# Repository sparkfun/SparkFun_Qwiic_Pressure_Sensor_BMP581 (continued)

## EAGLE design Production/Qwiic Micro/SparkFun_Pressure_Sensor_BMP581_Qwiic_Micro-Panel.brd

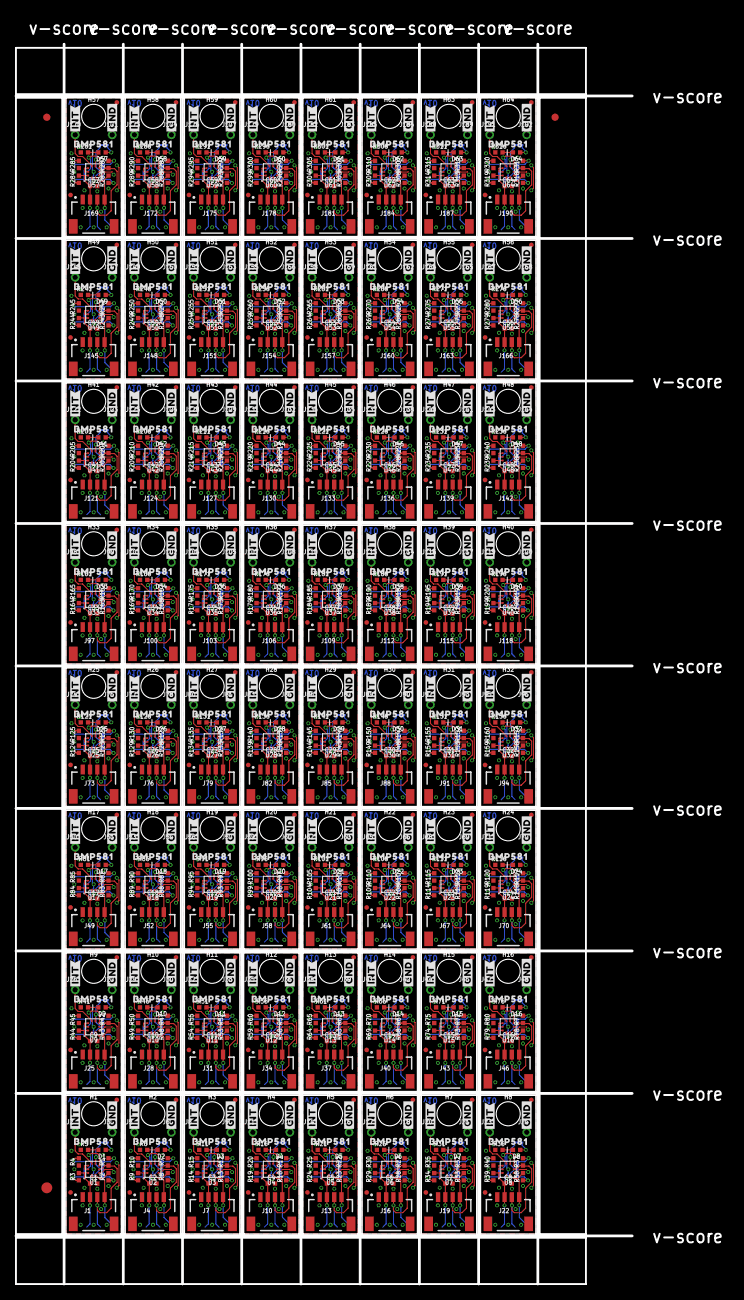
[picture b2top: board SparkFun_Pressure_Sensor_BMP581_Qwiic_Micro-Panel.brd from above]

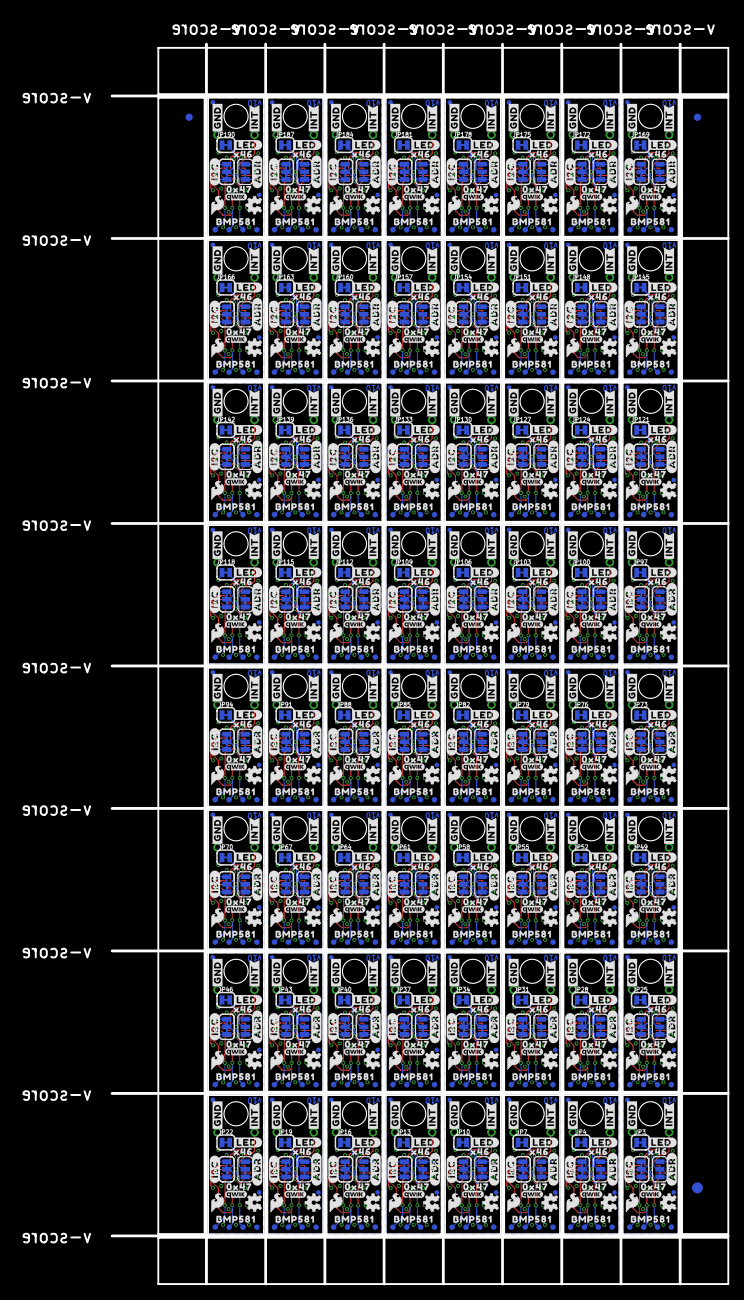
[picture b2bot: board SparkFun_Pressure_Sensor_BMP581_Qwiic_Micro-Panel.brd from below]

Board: 2 copper layers, 84.6 x 170.2 mm, 2502 parts (1283 on the bottom side), 768 nets.

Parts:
C1, C2, C3, C4, C5, C6, C7, C8, C9, C10, C11, C12, C13, C14, C15, C16, C17, C18, C19, C20, C21, C22, C23, C24, C25, C26, C27, C28, C29, C30, C31, C32, C33, C34, C35, C36, C37, C38, C39, C40, C41, C42, C43, C44, C45, C46, C47, C48, C49, C50, C51, C52, C53, C54, C55, C56, C57, C58, C59, C60, C61, C62, C63, C64: 0.1uF; 0402-TIGHT
D1, D2, D3, D4, D5, D6, D7, D8, D9, D10, D11, D12, D13, D14, D15, D16, D17, D18, D19, D20, D21, D22, D23, D24, D25, D26, D27, D28, D29, D30, D31, D32, D33, D34, D35, D36, D37, D38, D39, D40, D41, D42, D43, D44, D45, D46, D47, D48, D49, D50, D51, D52, D53, D54, D55, D56, D57, D58, D59, D60, D61, D62, D63, D64: RED; LED-0402
E$1, E$2, E$3, E$4: FIDUCIAL-1X2
E$5, E$6: FIDUCIAL-1.5X3
FD1, FD2, FD3, FD4, FD5, FD6, FD7, FD8, FD9, FD10, FD11, FD12, FD13, FD14, FD15, FD16, FD17, FD18, FD19, FD20, FD21, FD22, FD23, FD24, FD25, FD26, FD27, FD28, FD29, FD30, FD31, FD32, FD33, FD34, FD35, FD36, FD37, FD38, FD39, FD40, FD41, FD42, FD43, FD44, FD45, FD46, FD47, FD48, FD49, FD50, FD51, FD52, FD53, FD54, FD55, FD56, FD57, FD58, FD59, FD60, FD61, FD62, FD63, FD64, FD65, FD66, FD67, FD68, FD69, FD70, FD71, FD72, FD73, FD74, FD75, FD76, FD77, FD78, FD79, FD80, FD81, FD82, FD83, FD84, FD85, FD86, FD87, FD88, FD89, FD90, FD91, FD92, FD93, FD94, FD95, FD96, FD97, FD98, FD99, FD100, FD101, FD102, FD103, FD104, FD105, FD106, FD107, FD108, FD109, FD110, FD111, FD112, FD113, FD114, FD115, FD116, FD117, FD118, FD119, FD120, FD121, FD122, FD123, FD124, FD125, FD126, FD127, FD128, FD129, FD130, FD131, FD132, FD133, FD134, FD135, FD136, FD137, FD138, FD139, FD140, FD141, FD142, FD143, FD144, FD145, FD146, FD147, FD148, FD149, FD150, FD151, FD152, FD153, FD154, FD155, FD156, FD157, FD158, FD159, FD160, FD161, FD162, FD163, FD164, FD165, FD166, FD167, FD168, FD169, FD170, FD171, FD172, FD173, FD174, FD175, FD176, FD177, FD178, FD179, FD180, FD181, FD182, FD183, FD184, FD185, FD186, FD187, FD188, FD189, FD190, FD191, FD192, FD193, FD194, FD195, FD196, FD197, FD198, FD199, FD200, FD201, FD202, FD203, FD204, FD205, FD206, FD207, FD208, FD209, FD210, FD211, FD212, FD213, FD214, FD215, FD216, FD217, FD218, FD219, FD220, FD221, FD222, FD223, FD224, FD225, FD226, FD227, FD228, FD229, FD230, FD231, FD232, FD233, FD234, FD235, FD236, FD237, FD238, FD239, FD240, FD241, FD242, FD243, FD244, FD245, FD246, FD247, FD248, FD249, FD250, FD251, FD252, FD253, FD254, FD255, FD256: FIDUCIALUFIDUCIAL; FIDUCIAL-MICRO
FRAME1, FRAME2, FRAME3, FRAME4, FRAME5, FRAME6, FRAME7, FRAME8, FRAME9, FRAME10, FRAME11, FRAME12, FRAME13, FRAME14, FRAME15, FRAME16, FRAME17, FRAME18, FRAME19, FRAME20, FRAME21, FRAME22, FRAME23, FRAME24, FRAME25, FRAME26, FRAME27, FRAME28, FRAME29, FRAME30, FRAME31, FRAME32, FRAME33, FRAME34, FRAME35, FRAME36, FRAME37, FRAME38, FRAME39, FRAME40, FRAME41, FRAME42, FRAME43, FRAME44, FRAME45, FRAME46, FRAME47, FRAME48, FRAME49, FRAME50, FRAME51, FRAME52, FRAME53, FRAME54, FRAME55, FRAME56, FRAME57, FRAME58, FRAME59, FRAME60, FRAME61, FRAME62, FRAME63, FRAME64: FRAME-LETTER; CREATIVE_COMMONS
H1, H2, H3, H4, H5, H6, H7, H8, H9, H10, H11, H12, H13, H14, H15, H16, H17, H18, H19, H20, H21, H22, H23, H24, H25, H26, H27, H28, H29, H30, H31, H32, H33, H34, H35, H36, H37, H38, H39, H40, H41, H42, H43, H44, H45, H46, H47, H48, H49, H50, H51, H52, H53, H54, H55, H56, H57, H58, H59, H60, H61, H62, H63, H64: STAND-OFF
J1, J4, J7, J10, J13, J16, J19, J22, J25, J28, J31, J34, J37, J40, J43, J46, J49, J52, J55, J58, J61, J64, J67, J70, J73, J76, J79, J82, J85, J88, J91, J94, J97, J100, J103, J106, J109, J112, J115, J118, J121, J124, J127, J130, J133, J136, J139, J142, J145, J148, J151, J154, J157, J160, J163, J166, J169, J172, J175, J178, J181, J184, J187, J190: QWIIC_RIGHT_ANGLE; JST04_1MM_RA
J2, J3, J5, J6, J8, J9, J11, J12, J14, J15, J17, J18, J20, J21, J23, J24, J26, J27, J29, J30, J32, J33, J35, J36, J38, J39, J41, J42, J44, J45, J47, J48, J50, J51, J53, J54, J56, J57, J59, J60, J62, J63, J65, J66, J68, J69, J71, J72, J74, J75, J77, J78, J80, J81, J83, J84, J86, J87, J89, J90, J92, J93, J95, J96, J98, J99, J101, J102, J104, J105, J107, J108, J110, J111, J113, J114, J116, J117, J119, J120, J122, J123, J125, J126, J128, J129, J131, J132, J134, J135, J137, J138, J140, J141, J143, J144, J146, J147, J149, J150, J152, J153, J155, J156, J158, J159, J161, J162, J164, J165, J167, J168, J170, J171, J173, J174, J176, J177, J179, J180, J182, J183, J185, J186, J188, J189, J191, J192: 1X01_1MM_NO_SILK
JP1, JP6, JP9, JP12, JP15, JP18, JP21, JP24, JP27, JP30, JP33, JP36, JP39, JP42, JP45, JP48, JP51, JP54, JP57, JP60, JP63, JP66, JP69, JP72, JP75, JP78, JP81, JP84, JP87, JP90, JP93, JP96, JP99, JP102, JP105, JP108, JP111, JP114, JP117, JP120, JP123, JP126, JP129, JP132, JP135, JP138, JP141, JP144, JP147, JP150, JP153, JP156, JP159, JP162, JP165, JP168, JP171, JP174, JP177, JP180, JP183, JP186, JP189, JP192: ADR; SMT-JUMPER_3_1-NC_TRACE_SILK
JP2, JP5, JP8, JP11, JP14, JP17, JP20, JP23, JP26, JP29, JP32, JP35, JP38, JP41, JP44, JP47, JP50, JP53, JP56, JP59, JP62, JP65, JP68, JP71, JP74, JP77, JP80, JP83, JP86, JP89, JP92, JP95, JP98, JP101, JP104, JP107, JP110, JP113, JP116, JP119, JP122, JP125, JP128, JP131, JP134, JP137, JP140, JP143, JP146, JP149, JP152, JP155, JP158, JP161, JP164, JP167, JP170, JP173, JP176, JP179, JP182, JP185, JP188, JP191: I2C; SMT-JUMPER_3_2-NC_TRACE_SILK
JP3, JP4, JP7, JP10, JP13, JP16, JP19, JP22, JP25, JP28, JP31, JP34, JP37, JP40, JP43, JP46, JP49, JP52, JP55, JP58, JP61, JP64, JP67, JP70, JP73, JP76, JP79, JP82, JP85, JP88, JP91, JP94, JP97, JP100, JP103, JP106, JP109, JP112, JP115, JP118, JP121, JP124, JP127, JP130, JP133, JP136, JP139, JP142, JP145, JP148, JP151, JP154, JP157, JP160, JP163, JP166, JP169, JP172, JP175, JP178, JP181, JP184, JP187, JP190: LED; SMT-JUMPER_2_NC_TRACE_SILK
LOGO1, LOGO5, LOGO9, LOGO13, LOGO17, LOGO21, LOGO25, LOGO29, LOGO33, LOGO37, LOGO41, LOGO45, LOGO49, LOGO53, LOGO57, LOGO61, LOGO65, LOGO69, LOGO73, LOGO77, LOGO81, LOGO85, LOGO89, LOGO93, LOGO97, LOGO101, LOGO105, LOGO109, LOGO113, LOGO117, LOGO121, LOGO125, LOGO129, LOGO133, LOGO137, LOGO141, LOGO145, LOGO149, LOGO153, LOGO157, LOGO161, LOGO165, LOGO169, LOGO173, LOGO177, LOGO181, LOGO185, LOGO189, LOGO193, LOGO197, LOGO201, LOGO205, LOGO209, LOGO213, LOGO217, LOGO221, LOGO225, LOGO229, LOGO233, LOGO237, LOGO241, LOGO245, LOGO249, LOGO253: OSHW-LOGOMINI; OSHW-LOGO-MINI
LOGO2, LOGO6, LOGO10, LOGO14, LOGO18, LOGO22, LOGO26, LOGO30, LOGO34, LOGO38, LOGO42, LOGO46, LOGO50, LOGO54, LOGO58, LOGO62, LOGO66, LOGO70, LOGO74, LOGO78, LOGO82, LOGO86, LOGO90, LOGO94, LOGO98, LOGO102, LOGO106, LOGO110, LOGO114, LOGO118, LOGO122, LOGO126, LOGO130, LOGO134, LOGO138, LOGO142, LOGO146, LOGO150, LOGO154, LOGO158, LOGO162, LOGO166, LOGO170, LOGO174, LOGO178, LOGO182, LOGO186, LOGO190, LOGO194, LOGO198, LOGO202, LOGO206, LOGO210, LOGO214, LOGO218, LOGO222, LOGO226, LOGO230, LOGO234, LOGO238, LOGO242, LOGO246, LOGO250, LOGO254: SFE_LOGO_FLAME.1_INCH; SFE_LOGO_FLAME_.1
LOGO3, LOGO7, LOGO11, LOGO15, LOGO19, LOGO23, LOGO27, LOGO31, LOGO35, LOGO39, LOGO43, LOGO47, LOGO51, LOGO55, LOGO59, LOGO63, LOGO67, LOGO71, LOGO75, LOGO79, LOGO83, LOGO87, LOGO91, LOGO95, LOGO99, LOGO103, LOGO107, LOGO111, LOGO115, LOGO119, LOGO123, LOGO127, LOGO131, LOGO135, LOGO139, LOGO143, LOGO147, LOGO151, LOGO155, LOGO159, LOGO163, LOGO167, LOGO171, LOGO175, LOGO179, LOGO183, LOGO187, LOGO191, LOGO195, LOGO199, LOGO203, LOGO207, LOGO211, LOGO215, LOGO219, LOGO223, LOGO227, LOGO231, LOGO235, LOGO239, LOGO243, LOGO247, LOGO251, LOGO255: QWIIC_LOGO_3MM; QWIIC_3MM
LOGO4, LOGO8, LOGO12, LOGO16, LOGO20, LOGO24, LOGO28, LOGO32, LOGO36, LOGO40, LOGO44, LOGO48, LOGO52, LOGO56, LOGO60, LOGO64, LOGO68, LOGO72, LOGO76, LOGO80, LOGO84, LOGO88, LOGO92, LOGO96, LOGO100, LOGO104, LOGO108, LOGO112, LOGO116, LOGO120, LOGO124, LOGO128, LOGO132, LOGO136, LOGO140, LOGO144, LOGO148, LOGO152, LOGO156, LOGO160, LOGO164, LOGO168, LOGO172, LOGO176, LOGO180, LOGO184, LOGO188, LOGO192, LOGO196, LOGO200, LOGO204, LOGO208, LOGO212, LOGO216, LOGO220, LOGO224, LOGO228, LOGO232, LOGO236, LOGO240, LOGO244, LOGO248, LOGO252, LOGO256: SFE_LOGO_NAMEBLANK; BLANK
R1, R2, R7, R8, R12, R13, R17, R18, R22, R23, R27, R28, R32, R33, R37, R38, R42, R43, R47, R48, R52, R53, R57, R58, R62, R63, R67, R68, R72, R73, R77, R78, R82, R83, R87, R88, R92, R93, R97, R98, R102, R103, R107, R108, R112, R113, R117, R118, R122, R123, R127, R128, R132, R133, R137, R138, R142, R143, R147, R148, R152, R153, R157, R158, R162, R163, R167, R168, R172, R173, R177, R178, R182, R183, R187, R188, R192, R193, R197, R198, R202, R203, R207, R208, R212, R213, R217, R218, R222, R223, R227, R228, R232, R233, R237, R238, R242, R243, R247, R248, R252, R253, R257, R258, R262, R263, R267, R268, R272, R273, R277, R278, R282, R283, R287, R288, R292, R293, R297, R298, R302, R303, R307, R308, R312, R313, R317, R318: 2.2k; 0402-TIGHT
R3, R4, R9, R10, R14, R15, R19, R20, R24, R25, R29, R30, R34, R35, R39, R40, R44, R45, R49, R50, R54, R55, R59, R60, R64, R65, R69, R70, R74, R75, R79, R80, R84, R85, R89, R90, R94, R95, R99, R100, R104, R105, R109, R110, R114, R115, R119, R120, R124, R125, R129, R130, R134, R135, R139, R140, R144, R145, R149, R150, R154, R155, R159, R160, R164, R165, R169, R170, R174, R175, R179, R180, R184, R185, R189, R190, R194, R195, R199, R200, R204, R205, R209, R210, R214, R215, R219, R220, R224, R225, R229, R230, R234, R235, R239, R240, R244, R245, R249, R250, R254, R255, R259, R260, R264, R265, R269, R270, R274, R275, R279, R280, R284, R285, R289, R290, R294, R295, R299, R300, R304, R305, R309, R310, R314, R315, R319, R320: 10K; 0402-TIGHT
R5, R6, R11, R16, R21, R26, R31, R36, R41, R46, R51, R56, R61, R66, R71, R76, R81, R86, R91, R96, R101, R106, R111, R116, R121, R126, R131, R136, R141, R146, R151, R156, R161, R166, R171, R176, R181, R186, R191, R196, R201, R206, R211, R216, R221, R226, R231, R236, R241, R246, R251, R256, R261, R266, R271, R276, R281, R286, R291, R296, R301, R306, R311, R316: 1k; 0402-TIGHT
TP1, TP2, TP3, TP4, TP5, TP6, TP7, TP8, TP9, TP10, TP11, TP12, TP13, TP14, TP15, TP16, TP17, TP18, TP19, TP20, TP21, TP22, TP23, TP24, TP25, TP26, TP27, TP28, TP29, TP30, TP31, TP32, TP33, TP34, TP35, TP36, TP37, TP38, TP39, TP40, TP41, TP42, TP43, TP44, TP45, TP46, TP47, TP48, TP49, TP50, TP51, TP52, TP53, TP54, TP55, TP56, TP57, TP58, TP59, TP60, TP61, TP62, TP63, TP64, TP65, TP66, TP67, TP68, TP69, TP70, TP71, TP72, TP73, TP74, TP75, TP76, TP77, TP78, TP79, TP80, TP81, TP82, TP83, TP84, TP85, TP86, TP87, TP88, TP89, TP90, TP91, TP92, TP93, TP94, TP95, TP96, TP97, TP98, TP99, TP100, TP101, TP102, TP103, TP104, TP105, TP106, TP107, TP108, TP109, TP110, TP111, TP112, TP113, TP114, TP115, TP116, TP117, TP118, TP119, TP120, TP121, TP122, TP123, TP124, TP125, TP126, TP127, TP128, TP129, TP130, TP131, TP132, TP133, TP134, TP135, TP136, TP137, TP138, TP139, TP140, TP141, TP142, TP143, TP144, TP145, TP146, TP147, TP148, TP149, TP150, TP151, TP152, TP153, TP154, TP155, TP156, TP157, TP158, TP159, TP160, TP161, TP162, TP163, TP164, TP165, TP166, TP167, TP168, TP169, TP170, TP171, TP172, TP173, TP174, TP175, TP176, TP177, TP178, TP179, TP180, TP181, TP182, TP183, TP184, TP185, TP186, TP187, TP188, TP189, TP190, TP191, TP192, TP193, TP194, TP195, TP196, TP197, TP198, TP199, TP200, TP201, TP202, TP203, TP204, TP205, TP206, TP207, TP208, TP209, TP210, TP211, TP212, TP213, TP214, TP215, TP216, TP217, TP218, TP219, TP220, TP221, TP222, TP223, TP224, TP225, TP226, TP227, TP228, TP229, TP230, TP231, TP232, TP233, TP234, TP235, TP236, TP237, TP238, TP239, TP240, TP241, TP242, TP243, TP244, TP245, TP246, TP247, TP248, TP249, TP250, TP251, TP252, TP253, TP254, TP255, TP256: TEST-POINT3; PAD.03X.03
U1, U2, U3, U4, U5, U6, U7, U8, U9, U10, U11, U12, U13, U14, U15, U16, U17, U18, U19, U20, U21, U22, U23, U24, U25, U26, U27, U28, U29, U30, U31, U32, U33, U34, U35, U36, U37, U38, U39, U40, U41, U42, U43, U44, U45, U46, U47, U48, U49, U50, U51, U52, U53, U54, U55, U56, U57, U58, U59, U60, U61, U62, U63, U64: BMP581
U$1, U$2, U$16, U$17, U$27, U$28, U$38, U$39, U$49, U$50, U$60, U$61, U$71, U$72, U$82, U$83, U$93, U$94, U$104, U$105, U$115, U$116, U$126, U$127, U$137, U$138, U$148, U$149, U$159, U$160, U$170, U$171, U$181, U$182, U$192, U$193, U$203, U$204, U$214, U$215, U$225, U$226, U$236, U$237, U$247, U$248, U$258, U$259, U$269, U$270, U$280, U$281, U$291, U$292, U$302, U$303, U$313, U$314, U$324, U$325, U$335, U$336, U$346, U$347, U$357, U$358, U$368, U$369, U$379, U$380, U$390, U$391, U$401, U$402, U$412, U$413, U$423, U$424, U$434, U$435, U$445, U$446, U$456, U$457, U$467, U$468, U$478, U$479, U$489, U$490, U$500, U$501, U$511, U$512, U$522, U$523, U$533, U$534, U$544, U$545, U$555, U$556, U$566, U$567, U$577, U$578, U$588, U$589, U$599, U$600, U$610, U$611, U$621, U$622, U$632, U$633, U$643, U$644, U$654, U$655, U$665, U$666, U$676, U$677, U$687, U$688, U$698, U$699: BMP5810
U$3, U$18, U$29, U$40, U$51, U$62, U$73, U$84, U$95, U$106, U$117, U$128, U$139, U$150, U$161, U$172, U$183, U$194, U$205, U$216, U$227, U$238, U$249, U$260, U$271, U$282, U$293, U$304, U$315, U$326, U$337, U$348, U$359, U$370, U$381, U$392, U$403, U$414, U$425, U$436, U$447, U$458, U$469, U$480, U$491, U$502, U$513, U$524, U$535, U$546, U$557, U$568, U$579, U$590, U$601, U$612, U$623, U$634, U$645, U$656, U$667, U$678, U$689, U$700: #I2C#0
U$4, U$19, U$30, U$41, U$52, U$63, U$74, U$85, U$96, U$107, U$118, U$129, U$140, U$151, U$162, U$173, U$184, U$195, U$206, U$217, U$228, U$239, U$250, U$261, U$272, U$283, U$294, U$305, U$316, U$327, U$338, U$349, U$360, U$371, U$382, U$393, U$404, U$415, U$426, U$437, U$448, U$459, U$470, U$481, U$492, U$503, U$514, U$525, U$536, U$547, U$558, U$569, U$580, U$591, U$602, U$613, U$624, U$635, U$646, U$657, U$668, U$679, U$690, U$701: #ADR#0
U$5, U$6, U$12, U$13, U$23, U$24, U$34, U$35, U$45, U$46, U$56, U$57, U$67, U$68, U$78, U$79, U$89, U$90, U$100, U$101, U$111, U$112, U$122, U$123, U$133, U$134, U$144, U$145, U$155, U$156, U$166, U$167, U$177, U$178, U$188, U$189, U$199, U$200, U$210, U$211, U$221, U$222, U$232, U$233, U$243, U$244, U$254, U$255, U$265, U$266, U$276, U$277, U$287, U$288, U$298, U$299, U$309, U$310, U$320, U$321, U$331, U$332, U$342, U$343, U$353, U$354, U$364, U$365, U$375, U$376, U$386, U$387, U$397, U$398, U$408, U$409, U$419, U$420, U$430, U$431, U$441, U$442, U$452, U$453, U$463, U$464, U$474, U$475, U$485, U$486, U$496, U$497, U$507, U$508, U$518, U$519, U$529, U$530, U$540, U$541, U$551, U$552, U$562, U$563, U$573, U$574, U$584, U$585, U$595, U$596, U$606, U$607, U$617, U$618, U$628, U$629, U$639, U$640, U$650, U$651, U$661, U$662, U$672, U$673, U$683, U$684, U$694, U$695: #GND#0
U$7, U$8, U$14, U$15, U$25, U$26, U$36, U$37, U$47, U$48, U$58, U$59, U$69, U$70, U$80, U$81, U$91, U$92, U$102, U$103, U$113, U$114, U$124, U$125, U$135, U$136, U$146, U$147, U$157, U$158, U$168, U$169, U$179, U$180, U$190, U$191, U$201, U$202, U$212, U$213, U$223, U$224, U$234, U$235, U$245, U$246, U$256, U$257, U$267, U$268, U$278, U$279, U$289, U$290, U$300, U$301, U$311, U$312, U$322, U$323, U$333, U$334, U$344, U$345, U$355, U$356, U$366, U$367, U$377, U$378, U$388, U$389, U$399, U$400, U$410, U$411, U$421, U$422, U$432, U$433, U$443, U$444, U$454, U$455, U$465, U$466, U$476, U$477, U$487, U$488, U$498, U$499, U$509, U$510, U$520, U$521, U$531, U$532, U$542, U$543, U$553, U$554, U$564, U$565, U$575, U$576, U$586, U$587, U$597, U$598, U$608, U$609, U$619, U$620, U$630, U$631, U$641, U$642, U$652, U$653, U$663, U$664, U$674, U$675, U$685, U$686, U$696, U$697: #INT#0
U$9, U$20, U$31, U$42, U$53, U$64, U$75, U$86, U$97, U$108, U$119, U$130, U$141, U$152, U$163, U$174, U$185, U$196, U$207, U$218, U$229, U$240, U$251, U$262, U$273, U$284, U$295, U$306, U$317, U$328, U$339, U$350, U$361, U$372, U$383, U$394, U$405, U$416, U$427, U$438, U$449, U$460, U$471, U$482, U$493, U$504, U$515, U$526, U$537, U$548, U$559, U$570, U$581, U$592, U$603, U$614, U$625, U$636, U$647, U$658, U$669, U$680, U$691, U$702: #LED#0
U$10, U$21, U$32, U$43, U$54, U$65, U$76, U$87, U$98, U$109, U$120, U$131, U$142, U$153, U$164, U$175, U$186, U$197, U$208, U$219, U$230, U$241, U$252, U$263, U$274, U$285, U$296, U$307, U$318, U$329, U$340, U$351, U$362, U$373, U$384, U$395, U$406, U$417, U$428, U$439, U$450, U$461, U$472, U$483, U$494, U$505, U$516, U$527, U$538, U$549, U$560, U$571, U$582, U$593, U$604, U$615, U$626, U$637, U$648, U$659, U$670, U$681, U$692, U$703: X460
U$11, U$22, U$33, U$44, U$55, U$66, U$77, U$88, U$99, U$110, U$121, U$132, U$143, U$154, U$165, U$176, U$187, U$198, U$209, U$220, U$231, U$242, U$253, U$264, U$275, U$286, U$297, U$308, U$319, U$330, U$341, U$352, U$363, U$374, U$385, U$396, U$407, U$418, U$429, U$440, U$451, U$462, U$473, U$484, U$495, U$506, U$517, U$528, U$539, U$550, U$561, U$572, U$583, U$594, U$605, U$616, U$627, U$638, U$649, U$660, U$671, U$682, U$693, U$704: 0X470

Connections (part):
ADR: JP1.2, U1.5
ADR1: JP6.2, U2.5
ADR2: JP9.2, U3.5
ADR3: JP12.2, U4.5
ADR4: JP15.2, U5.5
ADR5: JP18.2, U6.5
ADR6: JP21.2, U7.5
ADR7: JP24.2, U8.5
ADR8: JP27.2, U9.5
ADR9: JP30.2, U10.5
ADR10: JP33.2, U11.5
ADR11: JP36.2, U12.5
ADR12: JP39.2, U13.5
ADR13: JP42.2, U14.5
ADR14: JP45.2, U15.5
ADR15: JP48.2, U16.5
ADR16: JP51.2, U17.5
ADR17: JP54.2, U18.5
ADR18: JP57.2, U19.5
ADR19: JP60.2, U20.5
ADR20: JP63.2, U21.5
ADR21: JP66.2, U22.5
ADR22: JP69.2, U23.5
ADR23: JP72.2, U24.5
ADR24: JP75.2, U25.5
ADR25: JP78.2, U26.5
ADR26: JP81.2, U27.5
ADR27: JP84.2, U28.5
ADR28: JP87.2, U29.5
ADR29: JP90.2, U30.5
ADR30: JP93.2, U31.5
ADR31: JP96.2, U32.5
ADR32: JP99.2, U33.5
ADR33: JP102.2, U34.5
ADR34: JP105.2, U35.5
ADR35: JP108.2, U36.5
ADR36: JP111.2, U37.5
ADR37: JP114.2, U38.5
ADR38: JP117.2, U39.5
ADR39: JP120.2, U40.5
ADR40: JP123.2, U41.5
ADR41: JP126.2, U42.5
ADR42: JP129.2, U43.5
ADR43: JP132.2, U44.5
ADR44: JP135.2, U45.5
ADR45: JP138.2, U46.5
ADR46: JP141.2, U47.5
ADR47: JP144.2, U48.5
ADR48: JP147.2, U49.5
ADR49: JP150.2, U50.5
ADR50: JP153.2, U51.5
ADR51: JP156.2, U52.5
ADR52: JP159.2, U53.5
ADR53: JP162.2, U54.5
ADR54: JP165.2, U55.5
ADR55: JP168.2, U56.5
ADR56: JP171.2, U57.5
ADR57: JP174.2, U58.5
ADR58: JP177.2, U59.5
ADR59: JP180.2, U60.5
ADR60: JP183.2, U61.5
ADR61: JP186.2, U62.5
ADR62: JP189.2, U63.5
ADR63: JP192.2, U64.5
GND: C1.2, J1.1, J3.1, R4.1, R5.1, TP1.1, U1.3, U1.8, U1.9
GND1: C2.2, J4.1, J6.1, R6.1, R10.1, TP5.1, U2.3, U2.8, U2.9
GND2: C3.2, J7.1, J9.1, R11.1, R15.1, TP9.1, U3.3, U3.8, U3.9
GND3: C4.2, J10.1, J12.1, R16.1, R20.1, TP13.1, U4.3, U4.8, U4.9
GND4: C5.2, J13.1, J15.1, R21.1, R25.1, TP17.1, U5.3, U5.8, U5.9
GND5: C6.2, J16.1, J18.1, R26.1, R30.1, TP21.1, U6.3, U6.8, U6.9
GND6: C7.2, J19.1, J21.1, R31.1, R35.1, TP25.1, U7.3, U7.8, U7.9
GND7: C8.2, J22.1, J24.1, R36.1, R40.1, TP29.1, U8.3, U8.8, U8.9
GND8: C9.2, J25.1, J27.1, R41.1, R45.1, TP33.1, U9.3, U9.8, U9.9
GND9: C10.2, J28.1, J30.1, R46.1, R50.1, TP37.1, U10.3, U10.8, U10.9
GND10: C11.2, J31.1, J33.1, R51.1, R55.1, TP41.1, U11.3, U11.8, U11.9
GND11: C12.2, J34.1, J36.1, R56.1, R60.1, TP45.1, U12.3, U12.8, U12.9
GND12: C13.2, J37.1, J39.1, R61.1, R65.1, TP49.1, U13.3, U13.8, U13.9
GND13: C14.2, J40.1, J42.1, R66.1, R70.1, TP53.1, U14.3, U14.8, U14.9
GND14: C15.2, J43.1, J45.1, R71.1, R75.1, TP57.1, U15.3, U15.8, U15.9
GND15: C16.2, J46.1, J48.1, R76.1, R80.1, TP61.1, U16.3, U16.8, U16.9
GND16: C17.2, J49.1, J51.1, R81.1, R85.1, TP65.1, U17.3, U17.8, U17.9
GND17: C18.2, J52.1, J54.1, R86.1, R90.1, TP69.1, U18.3, U18.8, U18.9
GND18: C19.2, J55.1, J57.1, R91.1, R95.1, TP73.1, U19.3, U19.8, U19.9
GND19: C20.2, J58.1, J60.1, R96.1, R100.1, TP77.1, U20.3, U20.8, U20.9
GND20: C21.2, J61.1, J63.1, R101.1, R105.1, TP81.1, U21.3, U21.8, U21.9
GND21: C22.2, J64.1, J66.1, R106.1, R110.1, TP85.1, U22.3, U22.8, U22.9
GND22: C23.2, J67.1, J69.1, R111.1, R115.1, TP89.1, U23.3, U23.8, U23.9
GND23: C24.2, J70.1, J72.1, R116.1, R120.1, TP93.1, U24.3, U24.8, U24.9
GND24: C25.2, J73.1, J75.1, R121.1, R125.1, TP97.1, U25.3, U25.8, U25.9
GND25: C26.2, J76.1, J78.1, R126.1, R130.1, TP101.1, U26.3, U26.8, U26.9
GND26: C27.2, J79.1, J81.1, R131.1, R135.1, TP105.1, U27.3, U27.8, U27.9
GND27: C28.2, J82.1, J84.1, R136.1, R140.1, TP109.1, U28.3, U28.8, U28.9
GND28: C29.2, J85.1, J87.1, R141.1, R145.1, TP113.1, U29.3, U29.8, U29.9
GND29: C30.2, J88.1, J90.1, R146.1, R150.1, TP117.1, U30.3, U30.8, U30.9
GND30: C31.2, J91.1, J93.1, R151.1, R155.1, TP121.1, U31.3, U31.8, U31.9
GND31: C32.2, J94.1, J96.1, R156.1, R160.1, TP125.1, U32.3, U32.8, U32.9
GND32: C33.2, J97.1, J99.1, R161.1, R165.1, TP129.1, U33.3, U33.8, U33.9
GND33: C34.2, J100.1, J102.1, R166.1, R170.1, TP133.1, U34.3, U34.8, U34.9
GND34: C35.2, J103.1, J105.1, R171.1, R175.1, TP137.1, U35.3, U35.8, U35.9
GND35: C36.2, J106.1, J108.1, R176.1, R180.1, TP141.1, U36.3, U36.8, U36.9
GND36: C37.2, J109.1, J111.1, R181.1, R185.1, TP145.1, U37.3, U37.8, U37.9
GND37: C38.2, J112.1, J114.1, R186.1, R190.1, TP149.1, U38.3, U38.8, U38.9
GND38: C39.2, J115.1, J117.1, R191.1, R195.1, TP153.1, U39.3, U39.8, U39.9
GND39: C40.2, J118.1, J120.1, R196.1, R200.1, TP157.1, U40.3, U40.8, U40.9
GND40: C41.2, J121.1, J123.1, R201.1, R205.1, TP161.1, U41.3, U41.8, U41.9
GND41: C42.2, J124.1, J126.1, R206.1, R210.1, TP165.1, U42.3, U42.8, U42.9
GND42: C43.2, J127.1, J129.1, R211.1, R215.1, TP169.1, U43.3, U43.8, U43.9
GND43: C44.2, J130.1, J132.1, R216.1, R220.1, TP173.1, U44.3, U44.8, U44.9
GND44: C45.2, J133.1, J135.1, R221.1, R225.1, TP177.1, U45.3, U45.8, U45.9
GND45: C46.2, J136.1, J138.1, R226.1, R230.1, TP181.1, U46.3, U46.8, U46.9
GND46: C47.2, J139.1, J141.1, R231.1, R235.1, TP185.1, U47.3, U47.8, U47.9
GND47: C48.2, J142.1, J144.1, R236.1, R240.1, TP189.1, U48.3, U48.8, U48.9
GND48: C49.2, J145.1, J147.1, R241.1, R245.1, TP193.1, U49.3, U49.8, U49.9
GND49: C50.2, J148.1, J150.1, R246.1, R250.1, TP197.1, U50.3, U50.8, U50.9
GND50: C51.2, J151.1, J153.1, R251.1, R255.1, TP201.1, U51.3, U51.8, U51.9
GND51: C52.2, J154.1, J156.1, R256.1, R260.1, TP205.1, U52.3, U52.8, U52.9
GND52: C53.2, J157.1, J159.1, R261.1, R265.1, TP209.1, U53.3, U53.8, U53.9
GND53: C54.2, J160.1, J162.1, R266.1, R270.1, TP213.1, U54.3, U54.8, U54.9
GND54: C55.2, J163.1, J165.1, R271.1, R275.1, TP217.1, U55.3, U55.8, U55.9
GND55: C56.2, J166.1, J168.1, R276.1, R280.1, TP221.1, U56.3, U56.8, U56.9
GND56: C57.2, J169.1, J171.1, R281.1, R285.1, TP225.1, U57.3, U57.8, U57.9
GND57: C58.2, J172.1, J174.1, R286.1, R290.1, TP229.1, U58.3, U58.8, U58.9
GND58: C59.2, J175.1, J177.1, R291.1, R295.1, TP233.1, U59.3, U59.8, U59.9
GND59: C60.2, J178.1, J180.1, R296.1, R300.1, TP237.1, U60.3, U60.8, U60.9
GND60: C61.2, J181.1, J183.1, R301.1, R305.1, TP241.1, U61.3, U61.8, U61.9
GND61: C62.2, J184.1, J186.1, R306.1, R310.1, TP245.1, U62.3, U62.8, U62.9
GND62: C63.2, J187.1, J189.1, R311.1, R315.1, TP249.1, U63.3, U63.8, U63.9
GND63: C64.2, J190.1, J192.1, R316.1, R320.1, TP253.1, U64.3, U64.8, U64.9
INT: J2.1, U1.7
INT1: J5.1, U2.7
INT2: J8.1, U3.7
INT3: J11.1, U4.7
INT4: J14.1, U5.7
INT5: J17.1, U6.7
INT6: J20.1, U7.7
INT7: J23.1, U8.7
INT8: J26.1, U9.7
INT9: J29.1, U10.7
INT10: J32.1, U11.7
INT11: J35.1, U12.7
INT12: J38.1, U13.7
INT13: J41.1, U14.7
INT14: J44.1, U15.7
INT15: J47.1, U16.7
INT16: J50.1, U17.7
INT17: J53.1, U18.7
INT18: J56.1, U19.7
INT19: J59.1, U20.7
INT20: J62.1, U21.7
INT21: J65.1, U22.7
INT22: J68.1, U23.7
INT23: J71.1, U24.7
INT24: J74.1, U25.7
INT25: J77.1, U26.7
INT26: J80.1, U27.7
INT27: J83.1, U28.7
INT28: J86.1, U29.7
INT29: J89.1, U30.7
INT30: J92.1, U31.7
INT31: J95.1, U32.7
INT32: J98.1, U33.7
INT33: J101.1, U34.7
INT34: J104.1, U35.7
INT35: J107.1, U36.7
INT36: J110.1, U37.7
INT37: J113.1, U38.7
INT38: J116.1, U39.7
INT39: J119.1, U40.7
INT40: J122.1, U41.7
INT41: J125.1, U42.7
INT42: J128.1, U43.7
INT43: J131.1, U44.7
INT44: J134.1, U45.7
INT45: J137.1, U46.7
INT46: J140.1, U47.7
INT47: J143.1, U48.7
INT48: J146.1, U49.7
INT49: J149.1, U50.7
INT50: J152.1, U51.7
INT51: J155.1, U52.7
INT52: J158.1, U53.7
INT53: J161.1, U54.7
INT54: J164.1, U55.7
INT55: J167.1, U56.7
INT56: J170.1, U57.7
INT57: J173.1, U58.7
INT58: J176.1, U59.7
INT59: J179.1, U60.7
INT60: J182.1, U61.7
INT61: J185.1, U62.7
INT62: J188.1, U63.7
INT63: J191.1, U64.7
unnamed: JP1.3, R3.1
unnamed: JP1.1, R4.2
unnamed: JP2.1, R2.1
unnamed: JP2.3, R1.2
unnamed: D1.A, JP3.1
unnamed: D1.C, R5.2
unnamed: D2.A, JP4.1
unnamed: D2.C, R6.2
unnamed: JP5.1, R8.1
unnamed: JP5.3, R7.2
unnamed: JP6.3, R9.1
unnamed: JP6.1, R10.2
unnamed: D3.A, JP7.1
unnamed: D3.C, R11.2
unnamed: JP8.1, R13.1
unnamed: JP8.3, R12.2
unnamed: JP9.3, R14.1
unnamed: JP9.1, R15.2
unnamed: D4.A, JP10.1
unnamed: D4.C, R16.2
unnamed: JP11.1, R18.1
unnamed: JP11.3, R17.2
unnamed: JP12.3, R19.1
unnamed: JP12.1, R20.2
unnamed: D5.A, JP13.1
unnamed: D5.C, R21.2
unnamed: JP14.1, R23.1
unnamed: JP14.3, R22.2
unnamed: JP15.3, R24.1
unnamed: JP15.1, R25.2
unnamed: D6.A, JP16.1
unnamed: D6.C, R26.2
unnamed: JP17.1, R28.1
unnamed: JP17.3, R27.2
unnamed: JP18.3, R29.1
unnamed: JP18.1, R30.2
unnamed: D7.A, JP19.1
unnamed: D7.C, R31.2
unnamed: JP20.1, R33.1
unnamed: JP20.3, R32.2
unnamed: JP21.3, R34.1
unnamed: JP21.1, R35.2
unnamed: D8.A, JP22.1
unnamed: D8.C, R36.2
unnamed: JP23.1, R38.1
unnamed: JP23.3, R37.2
unnamed: JP24.3, R39.1
unnamed: JP24.1, R40.2
unnamed: D9.A, JP25.1
unnamed: D9.C, R41.2
unnamed: JP26.1, R43.1
unnamed: JP26.3, R42.2
unnamed: JP27.3, R44.1
unnamed: JP27.1, R45.2
unnamed: D10.A, JP28.1
unnamed: D10.C, R46.2
unnamed: JP29.1, R48.1
unnamed: JP29.3, R47.2
unnamed: JP30.3, R49.1
unnamed: JP30.1, R50.2
unnamed: D11.A, JP31.1
unnamed: D11.C, R51.2
unnamed: JP32.1, R53.1
unnamed: JP32.3, R52.2
unnamed: JP33.3, R54.1
unnamed: JP33.1, R55.2
unnamed: D12.A, JP34.1
unnamed: D12.C, R56.2
unnamed: JP35.1, R58.1
unnamed: JP35.3, R57.2
unnamed: JP36.3, R59.1
unnamed: JP36.1, R60.2
unnamed: D13.A, JP37.1
unnamed: D13.C, R61.2
unnamed: JP38.1, R63.1
unnamed: JP38.3, R62.2
unnamed: JP39.3, R64.1
unnamed: JP39.1, R65.2
unnamed: D14.A, JP40.1
unnamed: D14.C, R66.2
unnamed: JP41.1, R68.1
unnamed: JP41.3, R67.2
unnamed: JP42.3, R69.1
unnamed: JP42.1, R70.2
unnamed: D15.A, JP43.1
unnamed: D15.C, R71.2
unnamed: JP44.1, R73.1
unnamed: JP44.3, R72.2
unnamed: JP45.3, R74.1
unnamed: JP45.1, R75.2
unnamed: D16.A, JP46.1
unnamed: D16.C, R76.2
unnamed: JP47.1, R78.1
unnamed: JP47.3, R77.2
unnamed: JP48.3, R79.1
unnamed: JP48.1, R80.2
unnamed: D17.A, JP49.1
unnamed: D17.C, R81.2
unnamed: JP50.1, R83.1
unnamed: JP50.3, R82.2
unnamed: JP51.3, R84.1
unnamed: JP51.1, R85.2
unnamed: D18.A, JP52.1
unnamed: D18.C, R86.2
unnamed: JP53.1, R88.1
unnamed: JP53.3, R87.2
unnamed: JP54.3, R89.1
unnamed: JP54.1, R90.2
unnamed: D19.A, JP55.1
unnamed: D19.C, R91.2
unnamed: JP56.1, R93.1
unnamed: JP56.3, R92.2
unnamed: JP57.3, R94.1
unnamed: JP57.1, R95.2
unnamed: D20.A, JP58.1
unnamed: D20.C, R96.2
unnamed: JP59.1, R98.1
unnamed: JP59.3, R97.2
unnamed: JP60.3, R99.1
unnamed: JP60.1, R100.2
unnamed: D21.A, JP61.1
unnamed: D21.C, R101.2
unnamed: JP62.1, R103.1
unnamed: JP62.3, R102.2
unnamed: JP63.3, R104.1
unnamed: JP63.1, R105.2
unnamed: D22.A, JP64.1
unnamed: D22.C, R106.2
unnamed: JP65.1, R108.1
unnamed: JP65.3, R107.2
unnamed: JP66.3, R109.1
unnamed: JP66.1, R110.2
unnamed: D23.A, JP67.1
unnamed: D23.C, R111.2
unnamed: JP68.1, R113.1
unnamed: JP68.3, R112.2
unnamed: JP69.3, R114.1
unnamed: JP69.1, R115.2
unnamed: D24.A, JP70.1
unnamed: D24.C, R116.2
unnamed: JP71.1, R118.1
unnamed: JP71.3, R117.2
unnamed: JP72.3, R119.1
unnamed: JP72.1, R120.2
unnamed: D25.A, JP73.1
unnamed: D25.C, R121.2
unnamed: JP74.1, R123.1
unnamed: JP74.3, R122.2
unnamed: JP75.3, R124.1
unnamed: JP75.1, R125.2
unnamed: D26.A, JP76.1
unnamed: D26.C, R126.2
unnamed: JP77.1, R128.1
unnamed: JP77.3, R127.2
unnamed: JP78.3, R129.1
unnamed: JP78.1, R130.2
unnamed: D27.A, JP79.1
unnamed: D27.C, R131.2
unnamed: JP80.1, R133.1
unnamed: JP80.3, R132.2
unnamed: JP81.3, R134.1
unnamed: JP81.1, R135.2
unnamed: D28.A, JP82.1
unnamed: D28.C, R136.2
unnamed: JP83.1, R138.1
unnamed: JP83.3, R137.2
unnamed: JP84.3, R139.1
unnamed: JP84.1, R140.2
unnamed: D29.A, JP85.1
unnamed: D29.C, R141.2
unnamed: JP86.1, R143.1
unnamed: JP86.3, R142.2
unnamed: JP87.3, R144.1
unnamed: JP87.1, R145.2
unnamed: D30.A, JP88.1
unnamed: D30.C, R146.2
unnamed: JP89.1, R148.1
unnamed: JP89.3, R147.2
unnamed: JP90.3, R149.1
unnamed: JP90.1, R150.2
unnamed: D31.A, JP91.1
unnamed: D31.C, R151.2
unnamed: JP92.1, R153.1
unnamed: JP92.3, R152.2
unnamed: JP93.3, R154.1
unnamed: JP93.1, R155.2
unnamed: D32.A, JP94.1
unnamed: D32.C, R156.2
unnamed: JP95.1, R158.1
unnamed: JP95.3, R157.2
unnamed: JP96.3, R159.1
unnamed: JP96.1, R160.2
unnamed: D33.A, JP97.1
unnamed: D33.C, R161.2
unnamed: JP98.1, R163.1
unnamed: JP98.3, R162.2
unnamed: JP99.3, R164.1
unnamed: JP99.1, R165.2
unnamed: D34.A, JP100.1
unnamed: D34.C, R166.2
unnamed: JP101.1, R168.1
unnamed: JP101.3, R167.2
unnamed: JP102.3, R169.1
unnamed: JP102.1, R170.2
unnamed: D35.A, JP103.1
unnamed: D35.C, R171.2
unnamed: JP104.1, R173.1
unnamed: JP104.3, R172.2
unnamed: JP105.3, R174.1
unnamed: JP105.1, R175.2
unnamed: D36.A, JP106.1
unnamed: D36.C, R176.2
unnamed: JP107.1, R178.1
unnamed: JP107.3, R177.2
unnamed: JP108.3, R179.1
unnamed: JP108.1, R180.2
unnamed: D37.A, JP109.1
unnamed: D37.C, R181.2
unnamed: JP110.1, R183.1
unnamed: JP110.3, R182.2
unnamed: JP111.3, R184.1
unnamed: JP111.1, R185.2
unnamed: D38.A, JP112.1
unnamed: D38.C, R186.2
unnamed: JP113.1, R188.1
unnamed: JP113.3, R187.2
unnamed: JP114.3, R189.1
unnamed: JP114.1, R190.2
unnamed: D39.A, JP115.1
unnamed: D39.C, R191.2
unnamed: JP116.1, R193.1
unnamed: JP116.3, R192.2
unnamed: JP117.3, R194.1
unnamed: JP117.1, R195.2
unnamed: D40.A, JP118.1
unnamed: D40.C, R196.2
unnamed: JP119.1, R198.1
unnamed: JP119.3, R197.2
unnamed: JP120.3, R199.1
unnamed: JP120.1, R200.2
unnamed: D41.A, JP121.1
unnamed: D41.C, R201.2
unnamed: JP122.1, R203.1
unnamed: JP122.3, R202.2
unnamed: JP123.3, R204.1
unnamed: JP123.1, R205.2
unnamed: D42.A, JP124.1
unnamed: D42.C, R206.2
unnamed: JP125.1, R208.1
unnamed: JP125.3, R207.2
unnamed: JP126.3, R209.1
unnamed: JP126.1, R210.2
unnamed: D43.A, JP127.1
unnamed: D43.C, R211.2
unnamed: JP128.1, R213.1
unnamed: JP128.3, R212.2
unnamed: JP129.3, R214.1
unnamed: JP129.1, R215.2
unnamed: D44.A, JP130.1
unnamed: D44.C, R216.2
unnamed: JP131.1, R218.1
unnamed: JP131.3, R217.2
unnamed: JP132.3, R219.1
unnamed: JP132.1, R220.2
unnamed: D45.A, JP133.1
unnamed: D45.C, R221.2
unnamed: JP134.1, R223.1
unnamed: JP134.3, R222.2
unnamed: JP135.3, R224.1
unnamed: JP135.1, R225.2
unnamed: D46.A, JP136.1
unnamed: D46.C, R226.2
unnamed: JP137.1, R228.1
unnamed: JP137.3, R227.2
unnamed: JP138.3, R229.1
unnamed: JP138.1, R230.2
unnamed: D47.A, JP139.1
unnamed: D47.C, R231.2
unnamed: JP140.1, R233.1
unnamed: JP140.3, R232.2
unnamed: JP141.3, R234.1
unnamed: JP141.1, R235.2
unnamed: D48.A, JP142.1
unnamed: D48.C, R236.2
unnamed: JP143.1, R238.1
unnamed: JP143.3, R237.2
unnamed: JP144.3, R239.1
unnamed: JP144.1, R240.2
unnamed: D49.A, JP145.1
unnamed: D49.C, R241.2
unnamed: JP146.1, R243.1
unnamed: JP146.3, R242.2
unnamed: JP147.3, R244.1
unnamed: JP147.1, R245.2
unnamed: D50.A, JP148.1
unnamed: D50.C, R246.2
unnamed: JP149.1, R248.1
unnamed: JP149.3, R247.2
unnamed: JP150.3, R249.1
unnamed: JP150.1, R250.2
unnamed: D51.A, JP151.1
unnamed: D51.C, R251.2
unnamed: JP152.1, R253.1
unnamed: JP152.3, R252.2
unnamed: JP153.3, R254.1
unnamed: JP153.1, R255.2
unnamed: D52.A, JP154.1
unnamed: D52.C, R256.2
unnamed: JP155.1, R258.1
unnamed: JP155.3, R257.2
unnamed: JP156.3, R259.1
unnamed: JP156.1, R260.2
unnamed: D53.A, JP157.1
unnamed: D53.C, R261.2
unnamed: JP158.1, R263.1
unnamed: JP158.3, R262.2
unnamed: JP159.3, R264.1
unnamed: JP159.1, R265.2
unnamed: D54.A, JP160.1
unnamed: D54.C, R266.2
unnamed: JP161.1, R268.1
unnamed: JP161.3, R267.2
unnamed: JP162.3, R269.1
unnamed: JP162.1, R270.2
unnamed: D55.A, JP163.1
unnamed: D55.C, R271.2
unnamed: JP164.1, R273.1
unnamed: JP164.3, R272.2
unnamed: JP165.3, R274.1
unnamed: JP165.1, R275.2
unnamed: D56.A, JP166.1
unnamed: D56.C, R276.2
unnamed: JP167.1, R278.1
unnamed: JP167.3, R277.2
unnamed: JP168.3, R279.1
unnamed: JP168.1, R280.2
unnamed: D57.A, JP169.1
unnamed: D57.C, R281.2
unnamed: JP170.1, R283.1
unnamed: JP170.3, R282.2
unnamed: JP171.3, R284.1
unnamed: JP171.1, R285.2
unnamed: D58.A, JP172.1
unnamed: D58.C, R286.2
unnamed: JP173.1, R288.1
unnamed: JP173.3, R287.2
unnamed: JP174.3, R289.1
unnamed: JP174.1, R290.2
unnamed: D59.A, JP175.1
unnamed: D59.C, R291.2
unnamed: JP176.1, R293.1
unnamed: JP176.3, R292.2
unnamed: JP177.3, R294.1
unnamed: JP177.1, R295.2
unnamed: D60.A, JP178.1
unnamed: D60.C, R296.2
unnamed: JP179.1, R298.1
unnamed: JP179.3, R297.2
unnamed: JP180.3, R299.1
unnamed: JP180.1, R300.2
unnamed: D61.A, JP181.1
unnamed: D61.C, R301.2
unnamed: JP182.1, R303.1
unnamed: JP182.3, R302.2
unnamed: JP183.3, R304.1
unnamed: JP183.1, R305.2
unnamed: D62.A, JP184.1
unnamed: D62.C, R306.2
unnamed: JP185.1, R308.1
unnamed: JP185.3, R307.2
unnamed: JP186.3, R309.1
unnamed: JP186.1, R310.2
unnamed: D63.A, JP187.1
unnamed: D63.C, R311.2
unnamed: JP188.1, R313.1
unnamed: JP188.3, R312.2
unnamed: JP189.3, R314.1
unnamed: JP189.1, R315.2
unnamed: D64.A, JP190.1
unnamed: D64.C, R316.2
unnamed: JP191.1, R318.1
unnamed: JP191.3, R317.2
unnamed: JP192.3, R319.1
unnamed: JP192.1, R320.2
SCL: J1.4, R2.2, TP4.1, U1.2
SCL1: J4.4, R8.2, TP8.1, U2.2
SCL2: J7.4, R13.2, TP12.1, U3.2
SCL3: J10.4, R18.2, TP16.1, U4.2
SCL4: J13.4, R23.2, TP20.1, U5.2
SCL5: J16.4, R28.2, TP24.1, U6.2
SCL6: J19.4, R33.2, TP28.1, U7.2
SCL7: J22.4, R38.2, TP32.1, U8.2
SCL8: J25.4, R43.2, TP36.1, U9.2
SCL9: J28.4, R48.2, TP40.1, U10.2
SCL10: J31.4, R53.2, TP44.1, U11.2
SCL11: J34.4, R58.2, TP48.1, U12.2
SCL12: J37.4, R63.2, TP52.1, U13.2
SCL13: J40.4, R68.2, TP56.1, U14.2
SCL14: J43.4, R73.2, TP60.1, U15.2
SCL15: J46.4, R78.2, TP64.1, U16.2
SCL16: J49.4, R83.2, TP68.1, U17.2
SCL17: J52.4, R88.2, TP72.1, U18.2
SCL18: J55.4, R93.2, TP76.1, U19.2
SCL19: J58.4, R98.2, TP80.1, U20.2
SCL20: J61.4, R103.2, TP84.1, U21.2
SCL21: J64.4, R108.2, TP88.1, U22.2
SCL22: J67.4, R113.2, TP92.1, U23.2
SCL23: J70.4, R118.2, TP96.1, U24.2
SCL24: J73.4, R123.2, TP100.1, U25.2
SCL25: J76.4, R128.2, TP104.1, U26.2
SCL26: J79.4, R133.2, TP108.1, U27.2
SCL27: J82.4, R138.2, TP112.1, U28.2
SCL28: J85.4, R143.2, TP116.1, U29.2
SCL29: J88.4, R148.2, TP120.1, U30.2
SCL30: J91.4, R153.2, TP124.1, U31.2
SCL31: J94.4, R158.2, TP128.1, U32.2
SCL32: J97.4, R163.2, TP132.1, U33.2
SCL33: J100.4, R168.2, TP136.1, U34.2
SCL34: J103.4, R173.2, TP140.1, U35.2
SCL35: J106.4, R178.2, TP144.1, U36.2
SCL36: J109.4, R183.2, TP148.1, U37.2
SCL37: J112.4, R188.2, TP152.1, U38.2
SCL38: J115.4, R193.2, TP156.1, U39.2
SCL39: J118.4, R198.2, TP160.1, U40.2
SCL40: J121.4, R203.2, TP164.1, U41.2
SCL41: J124.4, R208.2, TP168.1, U42.2
SCL42: J127.4, R213.2, TP172.1, U43.2
SCL43: J130.4, R218.2, TP176.1, U44.2
SCL44: J133.4, R223.2, TP180.1, U45.2
SCL45: J136.4, R228.2, TP184.1, U46.2
SCL46: J139.4, R233.2, TP188.1, U47.2
SCL47: J142.4, R238.2, TP192.1, U48.2
SCL48: J145.4, R243.2, TP196.1, U49.2
SCL49: J148.4, R248.2, TP200.1, U50.2
SCL50: J151.4, R253.2, TP204.1, U51.2
SCL51: J154.4, R258.2, TP208.1, U52.2
SCL52: J157.4, R263.2, TP212.1, U53.2
SCL53: J160.4, R268.2, TP216.1, U54.2
SCL54: J163.4, R273.2, TP220.1, U55.2
SCL55: J166.4, R278.2, TP224.1, U56.2
SCL56: J169.4, R283.2, TP228.1, U57.2
SCL57: J172.4, R288.2, TP232.1, U58.2
SCL58: J175.4, R293.2, TP236.1, U59.2
SCL59: J178.4, R298.2, TP240.1, U60.2
SCL60: J181.4, R303.2, TP244.1, U61.2
SCL61: J184.4, R308.2, TP248.1, U62.2
SCL62: J187.4, R313.2, TP252.1, U63.2
SCL63: J190.4, R318.2, TP256.1, U64.2
SDA: J1.3, R1.1, TP3.1, U1.4
SDA1: J4.3, R7.1, TP7.1, U2.4
SDA2: J7.3, R12.1, TP11.1, U3.4
SDA3: J10.3, R17.1, TP15.1, U4.4
SDA4: J13.3, R22.1, TP19.1, U5.4
SDA5: J16.3, R27.1, TP23.1, U6.4
SDA6: J19.3, R32.1, TP27.1, U7.4
SDA7: J22.3, R37.1, TP31.1, U8.4
SDA8: J25.3, R42.1, TP35.1, U9.4
SDA9: J28.3, R47.1, TP39.1, U10.4
SDA10: J31.3, R52.1, TP43.1, U11.4
SDA11: J34.3, R57.1, TP47.1, U12.4
SDA12: J37.3, R62.1, TP51.1, U13.4
SDA13: J40.3, R67.1, TP55.1, U14.4
SDA14: J43.3, R72.1, TP59.1, U15.4
SDA15: J46.3, R77.1, TP63.1, U16.4
SDA16: J49.3, R82.1, TP67.1, U17.4
SDA17: J52.3, R87.1, TP71.1, U18.4
SDA18: J55.3, R92.1, TP75.1, U19.4
SDA19: J58.3, R97.1, TP79.1, U20.4
SDA20: J61.3, R102.1, TP83.1, U21.4
SDA21: J64.3, R107.1, TP87.1, U22.4
SDA22: J67.3, R112.1, TP91.1, U23.4
SDA23: J70.3, R117.1, TP95.1, U24.4
SDA24: J73.3, R122.1, TP99.1, U25.4
SDA25: J76.3, R127.1, TP103.1, U26.4
SDA26: J79.3, R132.1, TP107.1, U27.4
SDA27: J82.3, R137.1, TP111.1, U28.4
SDA28: J85.3, R142.1, TP115.1, U29.4
SDA29: J88.3, R147.1, TP119.1, U30.4
SDA30: J91.3, R152.1, TP123.1, U31.4
SDA31: J94.3, R157.1, TP127.1, U32.4
SDA32: J97.3, R162.1, TP131.1, U33.4
SDA33: J100.3, R167.1, TP135.1, U34.4
SDA34: J103.3, R172.1, TP139.1, U35.4
SDA35: J106.3, R177.1, TP143.1, U36.4
SDA36: J109.3, R182.1, TP147.1, U37.4
SDA37: J112.3, R187.1, TP151.1, U38.4
SDA38: J115.3, R192.1, TP155.1, U39.4
SDA39: J118.3, R197.1, TP159.1, U40.4
SDA40: J121.3, R202.1, TP163.1, U41.4
SDA41: J124.3, R207.1, TP167.1, U42.4
SDA42: J127.3, R212.1, TP171.1, U43.4
SDA43: J130.3, R217.1, TP175.1, U44.4
SDA44: J133.3, R222.1, TP179.1, U45.4
SDA45: J136.3, R227.1, TP183.1, U46.4
SDA46: J139.3, R232.1, TP187.1, U47.4
SDA47: J142.3, R237.1, TP191.1, U48.4
SDA48: J145.3, R242.1, TP195.1, U49.4
SDA49: J148.3, R247.1, TP199.1, U50.4
SDA50: J151.3, R252.1, TP203.1, U51.4
SDA51: J154.3, R257.1, TP207.1, U52.4
SDA52: J157.3, R262.1, TP211.1, U53.4
SDA53: J160.3, R267.1, TP215.1, U54.4
SDA54: J163.3, R272.1, TP219.1, U55.4
SDA55: J166.3, R277.1, TP223.1, U56.4
SDA56: J169.3, R282.1, TP227.1, U57.4
SDA57: J172.3, R287.1, TP231.1, U58.4
SDA58: J175.3, R292.1, TP235.1, U59.4
SDA59: J178.3, R297.1, TP239.1, U60.4
SDA60: J181.3, R302.1, TP243.1, U61.4
SDA61: J184.3, R307.1, TP247.1, U62.4
SDA62: J187.3, R312.1, TP251.1, U63.4
SDA63: J190.3, R317.1, TP255.1, U64.4
VDD: C1.1, J1.2, JP2.2, JP3.2, R3.2, TP2.1, U1.1, U1.6, U1.10
VDD1: C2.1, J4.2, JP4.2, JP5.2, R9.2, TP6.1, U2.1, U2.6, U2.10
VDD2: C3.1, J7.2, JP7.2, JP8.2, R14.2, TP10.1, U3.1, U3.6, U3.10
VDD3: C4.1, J10.2, JP10.2, JP11.2, R19.2, TP14.1, U4.1, U4.6, U4.10
VDD4: C5.1, J13.2, JP13.2, JP14.2, R24.2, TP18.1, U5.1, U5.6, U5.10
VDD5: C6.1, J16.2, JP16.2, JP17.2, R29.2, TP22.1, U6.1, U6.6, U6.10
VDD6: C7.1, J19.2, JP19.2, JP20.2, R34.2, TP26.1, U7.1, U7.6, U7.10
VDD7: C8.1, J22.2, JP22.2, JP23.2, R39.2, TP30.1, U8.1, U8.6, U8.10
VDD8: C9.1, J25.2, JP25.2, JP26.2, R44.2, TP34.1, U9.1, U9.6, U9.10
VDD9: C10.1, J28.2, JP28.2, JP29.2, R49.2, TP38.1, U10.1, U10.6, U10.10
VDD10: C11.1, J31.2, JP31.2, JP32.2, R54.2, TP42.1, U11.1, U11.6, U11.10
VDD11: C12.1, J34.2, JP34.2, JP35.2, R59.2, TP46.1, U12.1, U12.6, U12.10
VDD12: C13.1, J37.2, JP37.2, JP38.2, R64.2, TP50.1, U13.1, U13.6, U13.10
VDD13: C14.1, J40.2, JP40.2, JP41.2, R69.2, TP54.1, U14.1, U14.6, U14.10
VDD14: C15.1, J43.2, JP43.2, JP44.2, R74.2, TP58.1, U15.1, U15.6, U15.10
VDD15: C16.1, J46.2, JP46.2, JP47.2, R79.2, TP62.1, U16.1, U16.6, U16.10
VDD16: C17.1, J49.2, JP49.2, JP50.2, R84.2, TP66.1, U17.1, U17.6, U17.10
VDD17: C18.1, J52.2, JP52.2, JP53.2, R89.2, TP70.1, U18.1, U18.6, U18.10
VDD18: C19.1, J55.2, JP55.2, JP56.2, R94.2, TP74.1, U19.1, U19.6, U19.10
VDD19: C20.1, J58.2, JP58.2, JP59.2, R99.2, TP78.1, U20.1, U20.6, U20.10
VDD20: C21.1, J61.2, JP61.2, JP62.2, R104.2, TP82.1, U21.1, U21.6, U21.10
VDD21: C22.1, J64.2, JP64.2, JP65.2, R109.2, TP86.1, U22.1, U22.6, U22.10
VDD22: C23.1, J67.2, JP67.2, JP68.2, R114.2, TP90.1, U23.1, U23.6, U23.10
VDD23: C24.1, J70.2, JP70.2, JP71.2, R119.2, TP94.1, U24.1, U24.6, U24.10
VDD24: C25.1, J73.2, JP73.2, JP74.2, R124.2, TP98.1, U25.1, U25.6, U25.10
VDD25: C26.1, J76.2, JP76.2, JP77.2, R129.2, TP102.1, U26.1, U26.6, U26.10
VDD26: C27.1, J79.2, JP79.2, JP80.2, R134.2, TP106.1, U27.1, U27.6, U27.10
VDD27: C28.1, J82.2, JP82.2, JP83.2, R139.2, TP110.1, U28.1, U28.6, U28.10
VDD28: C29.1, J85.2, JP85.2, JP86.2, R144.2, TP114.1, U29.1, U29.6, U29.10
VDD29: C30.1, J88.2, JP88.2, JP89.2, R149.2, TP118.1, U30.1, U30.6, U30.10
VDD30: C31.1, J91.2, JP91.2, JP92.2, R154.2, TP122.1, U31.1, U31.6, U31.10
VDD31: C32.1, J94.2, JP94.2, JP95.2, R159.2, TP126.1, U32.1, U32.6, U32.10
VDD32: C33.1, J97.2, JP97.2, JP98.2, R164.2, TP130.1, U33.1, U33.6, U33.10
VDD33: C34.1, J100.2, JP100.2, JP101.2, R169.2, TP134.1, U34.1, U34.6, U34.10
VDD34: C35.1, J103.2, JP103.2, JP104.2, R174.2, TP138.1, U35.1, U35.6, U35.10
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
